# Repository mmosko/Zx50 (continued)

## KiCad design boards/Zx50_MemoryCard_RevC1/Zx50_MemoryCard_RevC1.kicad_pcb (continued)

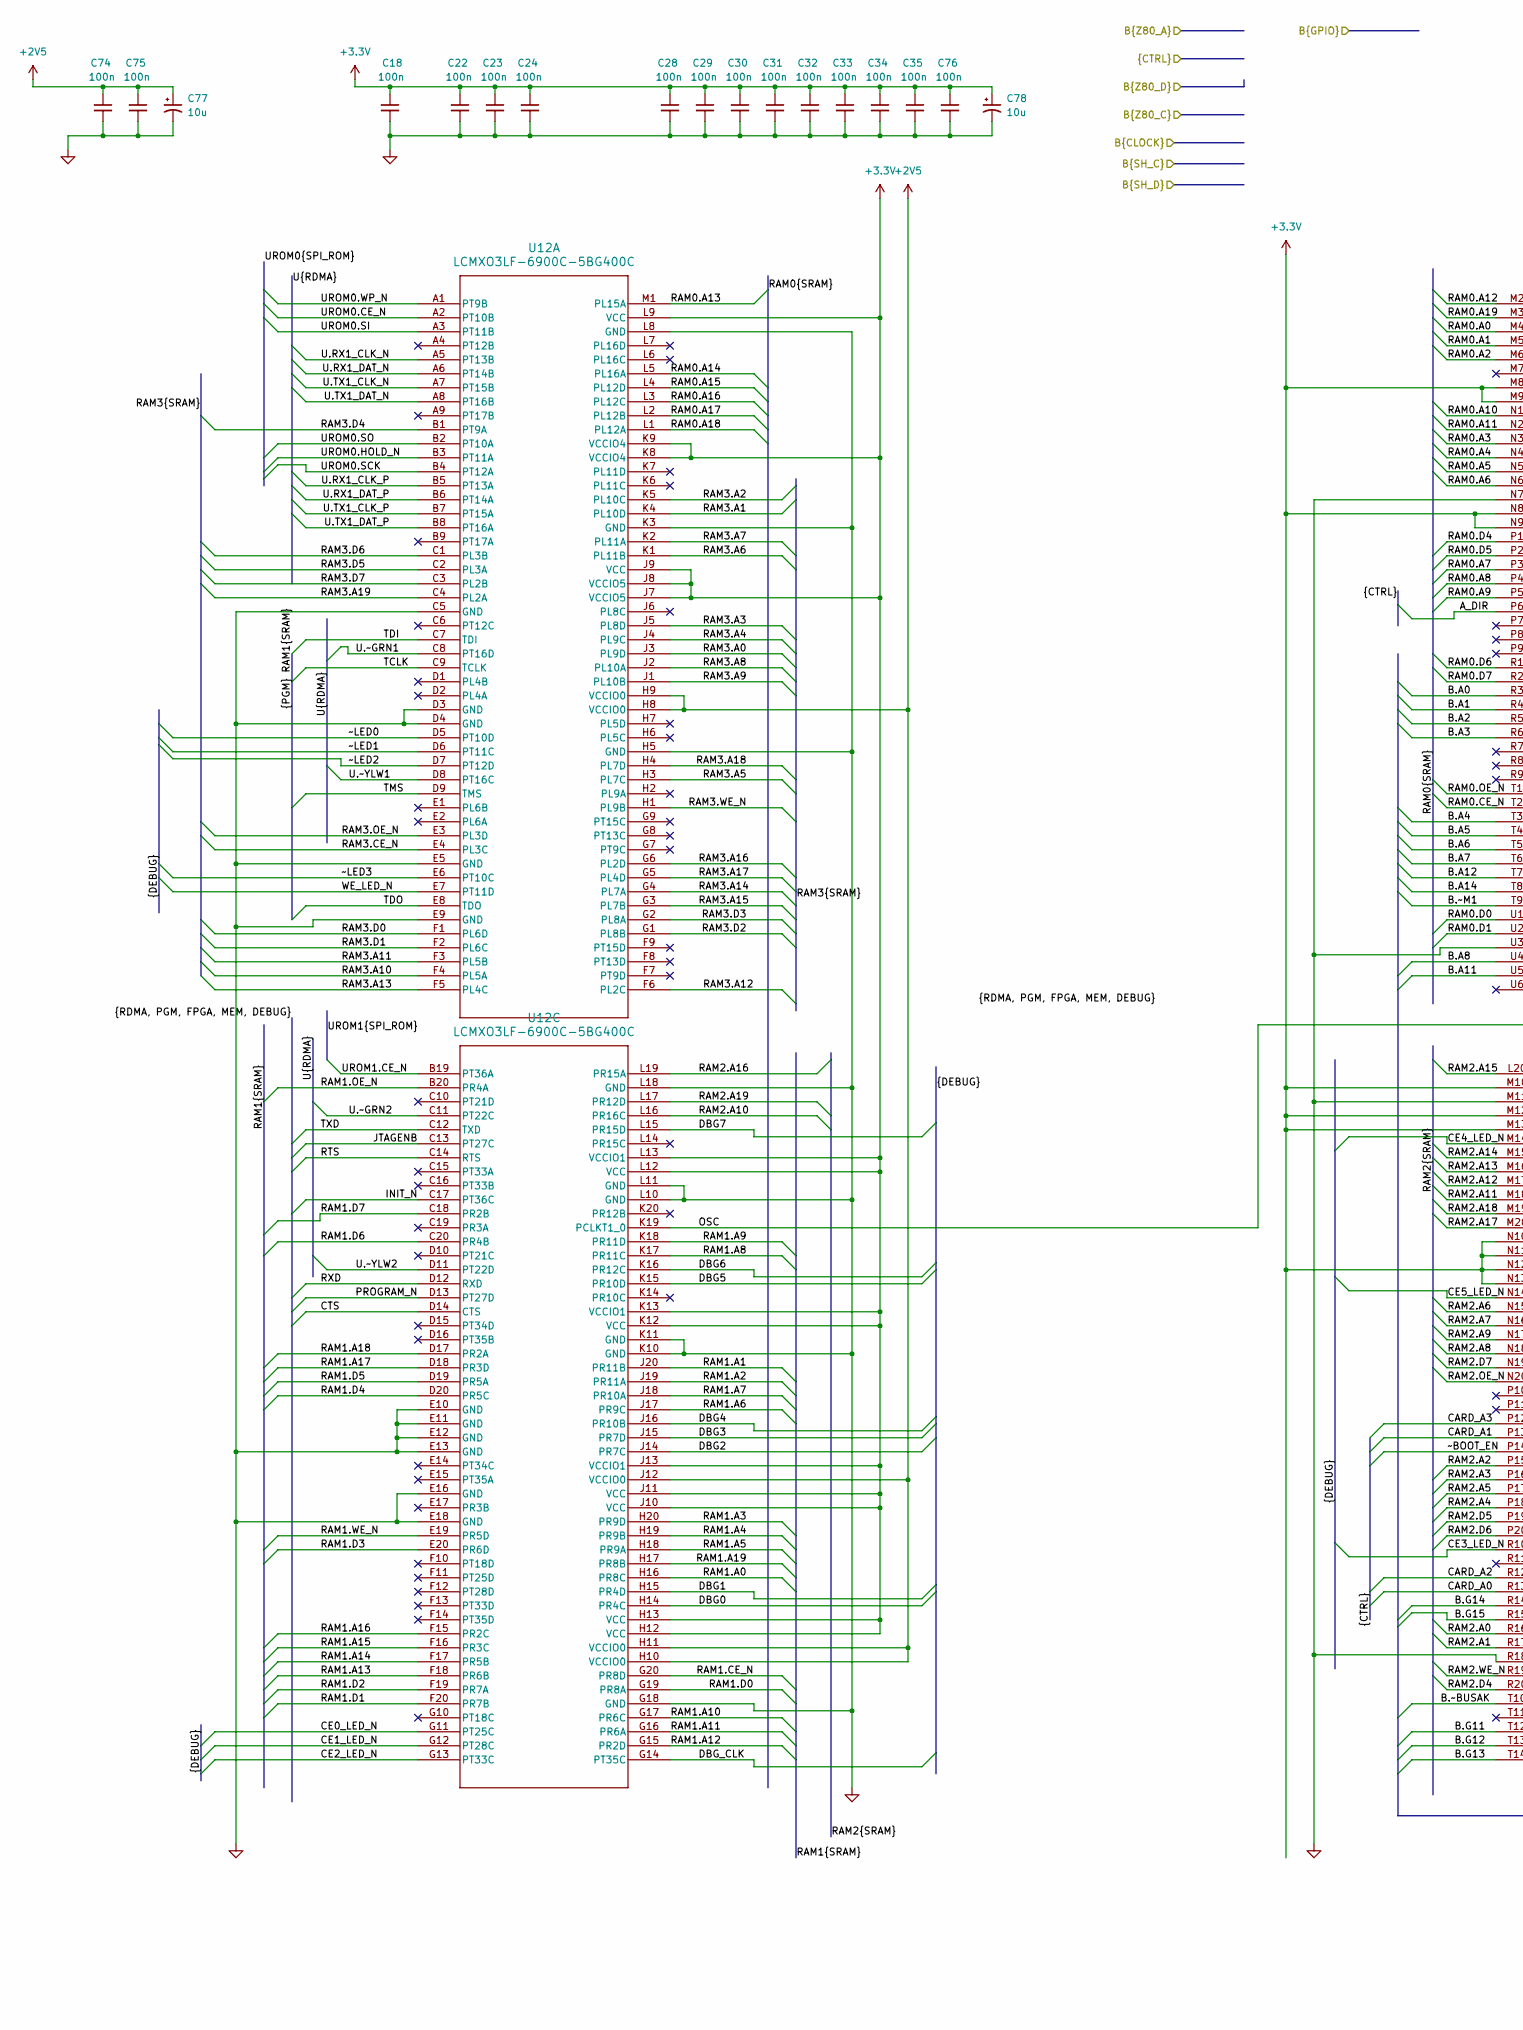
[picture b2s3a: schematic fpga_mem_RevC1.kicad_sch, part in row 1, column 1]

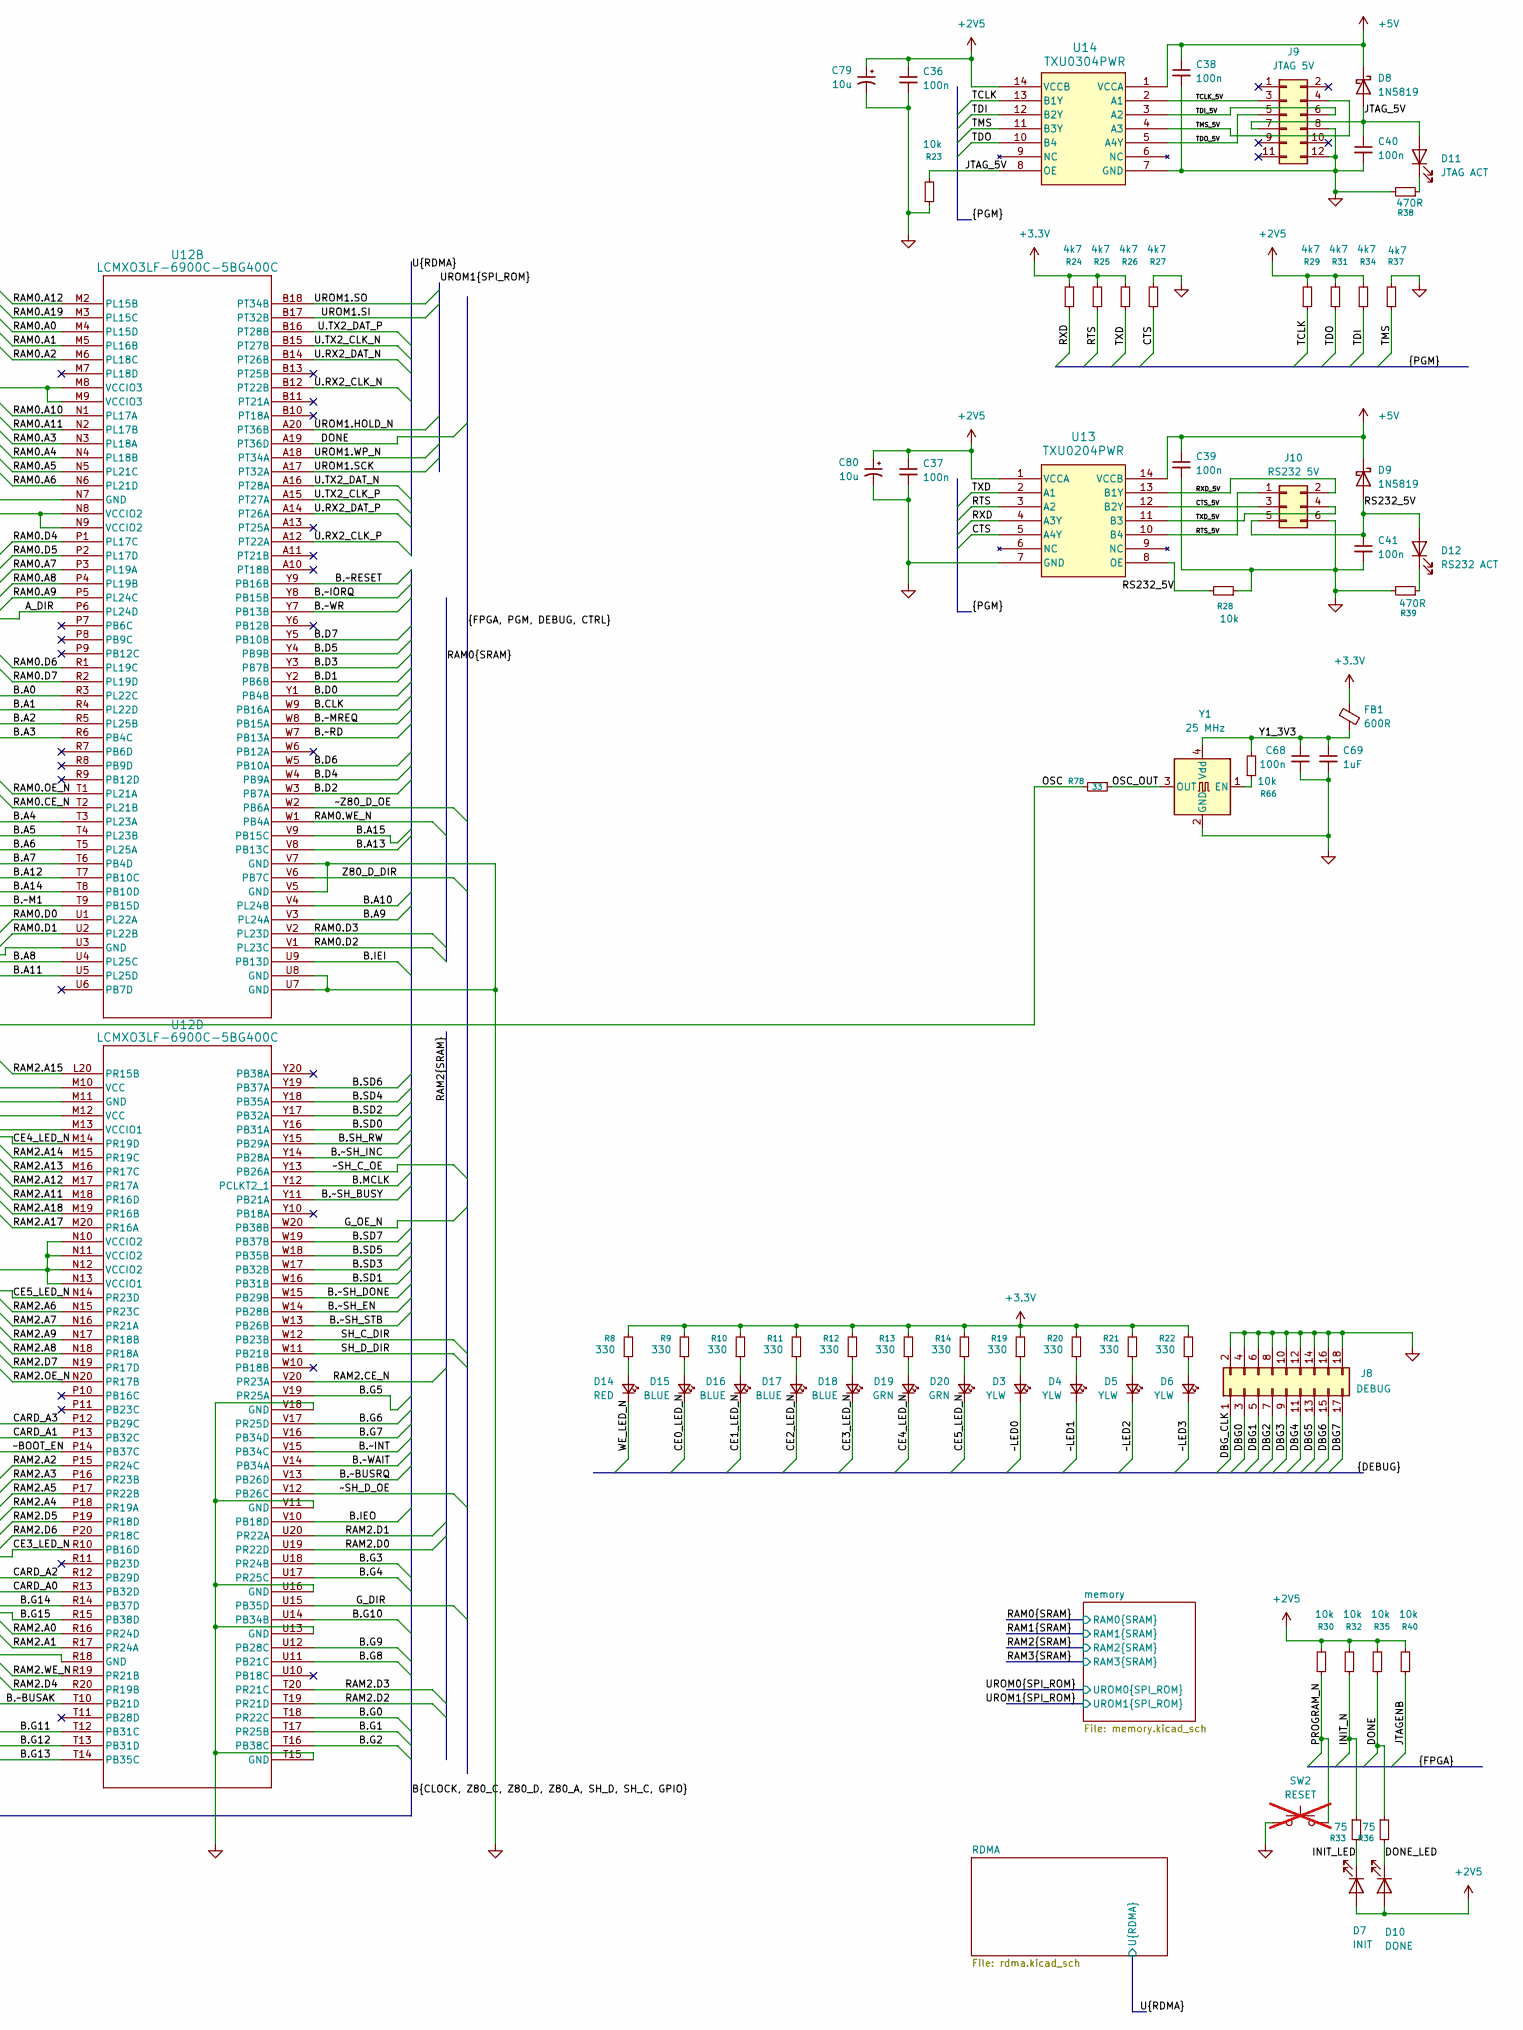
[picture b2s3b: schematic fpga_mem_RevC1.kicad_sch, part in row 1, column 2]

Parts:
C18, C22, C23, C24, C28, C29, C30, C31, C32, C33, C34, C35, C36, C37, C38, C39, C40, C41, C68, C74, C75, C76: 100n; C_0402_1005Metric; LCSC C1525
C69: 1uF; C_0402_1005Metric; LCSC C52923
C77, C78, C79, C80: 10u; C_1206_3216Metric; MFG PN AVX TAJA106K016RNJ Tantalinium; LCSC C7171
D3, D4, D5, D6: YLW; LED_0805_2012Metric; MFG_PN KT-0805Y; LCSC C2296
D7: INIT; LED_D3.0mm
D8, D9: 1N5819; D_SOD-323; LCSC C191023
D10: DONE; LED_D3.0mm
D11: JTAG ACT; LED_D3.0mm
D12: RS232 ACT; LED_D3.0mm
D14: RED; LED_0805_2012Metric; MFG_PN NCD0805R1; LCSC C84256
D15, D16, D17, D18: BLUE; LED_0805_2012Metric; MFG_PN KT-0805B; LCSC C2293
D19, D20: GRN; LED_0805_2012Metric; MFG_PN KT-0805G; LCSC C2297
FB1: 600R; 0805; LCSC C1017
J8: DEBUG; IDC-Header_2x09_P2.54mm_Vertical
J9: JTAG 5V; IDC-Header_2x06_P2.54mm_Horizontal
J10: RS232 5V; IDC-Header_2x03_P2.54mm_Horizontal
R8, R9, R10, R11, R12, R13, R14, R19, R20, R21, R22: 330; R_0805_2012Metric; MFG_PN 0805W8F3300T5E; LCSC C17630
R23, R28, R30, R32, R35, R40, R66: 10k; R_0402_1005Metric; MFG_PN 0402WGF1002TCE; LCSC C25744
R24, R25, R26, R27, R29, R31, R34, R37: 4k7; R_0402_1005Metric; MFG_PN 0402WGF4701TCE; LCSC C25900
R33, R36: 75; R_0603_1608Metric; MFG_PN 0603WAF750JT5E; LCSC C4275
R38, R39: 470R; R_0805_2012Metric; MFG_PN 0805W8F4700T5E; LCSC C17710
R78: 33; R_0402_1005Metric; MFG_PN 0402WGF1000TCE; LCSC C25076
SW2: RESET; SW_PUSH_6mm_H7.3mm; DigiKey_PN SW402-ND; not fitted
U12: LCMXO3LF-6900C-5BG400C; CABGA400_LAT
U13: TXU0204PWR; TSSOP14_PW_TEX; LCSC C4363888
U14: TXU0304PWR; TSSOP14_PW_TEX; LCSC C4364118
Y1: 25 MHz; Crystal_SMD_3225-4Pin_3.2x2.5mm; LCSC C669088

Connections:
+2V5: C36.1, C37.1, C74.1, C75.1, C77.1, C79.1, C80.1, D7.2 (A), D10.2 (A), R29.2, R30.2, R31.2, R32.2, R34.2, R35.2, R40.2, U12.H8 (VCCIO0), U12.H9 (VCCIO0), U12.H10 (VCCIO0), U12.H11 (VCCIO0), U12.J12 (VCCIO0), U13.1 (VCCA), U14.14 (VCCB); also elsewhere on the board
+3.3V: C18.1, C22.1, C23.1, C24.1, C28.1, C29.1, C30.1, C31.1, C32.1, C33.1, C34.1, C35.1, C76.1, C78.1, FB1.1, R8.2, R9.2, R10.2, R11.2, R12.2, R13.2, R14.2, R19.2, R20.2, R21.2, R22.2, R24.2, R25.2, R26.2, U12.H12 (VCC), U12.H13 (VCC), U12.J7 (VCCIO5), U12.J8 (VCCIO5), U12.J9 (VCC), U12.J10 (VCC), U12.J11 (VCC), U12.J13 (VCCIO1), U12.K8 (VCCIO4), U12.K9 (VCCIO4), U12.K12 (VCC), U12.K13 (VCCIO1), U12.L9 (VCC), U12.L12 (VCC), U12.L13 (VCCIO1), U12.M8 (VCCIO3), U12.M9 (VCCIO3), U12.M10 (VCC), U12.M12 (VCC), U12.M13 (VCCIO1), U12.N8 (VCCIO2), U12.N9 (VCCIO2), U12.N10 (VCCIO2), U12.N11 (VCCIO2), U12.N12 (VCCIO2), U12.N13 (VCCIO1); also elsewhere on the board
+5V: C38.1, C39.1, D8.1 (K), D9.1 (K), U13.14 (VCCB), U14.1 (VCCA); also elsewhere on the board
/A_DIR: U12.P6 (PL24D); also elsewhere on the board
/B.A0: U12.R3 (PL22C); also elsewhere on the board
/B.A1: U12.R4 (PL22D); also elsewhere on the board
/B.A2: U12.R5 (PL25B); also elsewhere on the board
/B.A3: U12.R6 (PB4C); also elsewhere on the board
/B.A4: U12.T3 (PL23A); also elsewhere on the board
/B.A5: U12.T4 (PL23B); also elsewhere on the board
/B.A6: U12.T5 (PL25A); also elsewhere on the board
/B.A7: U12.T6 (PB4D); also elsewhere on the board
/B.A8: U12.U4 (PL25C); also elsewhere on the board
/B.A9: U12.V3 (PL24A); also elsewhere on the board
/B.A10: U12.V4 (PL24B); also elsewhere on the board
/B.A11: U12.U5 (PL25D); also elsewhere on the board
/B.A12: U12.T7 (PB10C); also elsewhere on the board
/B.A13: U12.V8 (PB13C); also elsewhere on the board
/B.A14: U12.T8 (PB10D); also elsewhere on the board
/B.A15: U12.V9 (PB15C); also elsewhere on the board
/B.CLK: U12.W9 (PB16A); also elsewhere on the board
/B.D0: U12.Y1 (PB4B); also elsewhere on the board
/B.D1: U12.Y2 (PB6B); also elsewhere on the board
/B.D2: U12.W3 (PB7A); also elsewhere on the board
/B.D3: U12.Y3 (PB7B); also elsewhere on the board
/B.D4: U12.W4 (PB9A); also elsewhere on the board
/B.D5: U12.Y4 (PB9B); also elsewhere on the board
/B.D6: U12.W5 (PB10A); also elsewhere on the board
/B.D7: U12.Y5 (PB10B); also elsewhere on the board
/B.G0: U12.T18 (PR22C); also elsewhere on the board
/B.G1: U12.T17 (PR25B); also elsewhere on the board
/B.G2: U12.T16 (PB38C); also elsewhere on the board
/B.G3: U12.U18 (PR24B); also elsewhere on the board
/B.G4: U12.U17 (PR25C); also elsewhere on the board
/B.G5: U12.V19 (PR25A); also elsewhere on the board
/B.G6: U12.V17 (PR25D); also elsewhere on the board
/B.G7: U12.V16 (PB34D); also elsewhere on the board
/B.G8: U12.U11 (PB21C); also elsewhere on the board
/B.G9: U12.U12 (PB28C); also elsewhere on the board
/B.G10: U12.U14 (PB34B); also elsewhere on the board
/B.G11: U12.T12 (PB31C); also elsewhere on the board
/B.G12: U12.T13 (PB31D); also elsewhere on the board
/B.G13: U12.T14 (PB35C); also elsewhere on the board
/B.G14: U12.R14 (PB37D); also elsewhere on the board
/B.G15: U12.R15 (PB38D); also elsewhere on the board
/B.IEI: U12.U9 (PB13D); also elsewhere on the board
/B.IEO: U12.V10 (PB18D); also elsewhere on the board
/B.MCLK: U12.Y12 (PCLKT2_1); also elsewhere on the board
/B.SD0: U12.Y16 (PB31A); also elsewhere on the board
/B.SD1: U12.W16 (PB31B); also elsewhere on the board
/B.SD2: U12.Y17 (PB32A); also elsewhere on the board
/B.SD3: U12.W17 (PB32B); also elsewhere on the board
/B.SD4: U12.Y18 (PB35A); also elsewhere on the board
/B.SD5: U12.W18 (PB35B); also elsewhere on the board
/B.SD6: U12.Y19 (PB37A); also elsewhere on the board
/B.SD7: U12.W19 (PB37B); also elsewhere on the board
/B.SH_RW: U12.Y15 (PB29A); also elsewhere on the board
/B.~BUSAK: U12.T10 (PB21D); also elsewhere on the board
/B.~BUSRQ: U12.V13 (PB26D); also elsewhere on the board
/B.~INT: U12.V15 (PB34C); also elsewhere on the board
/B.~IORQ: U12.Y8 (PB15B); also elsewhere on the board
/B.~M1: U12.T9 (PB15D); also elsewhere on the board
/B.~MREQ: U12.W8 (PB15A); also elsewhere on the board
/B.~RD: U12.W7 (PB13A); also elsewhere on the board
/B.~RESET: U12.Y9 (PB16B); also elsewhere on the board
/B.~SH_BUSY: U12.Y11 (PB21A); also elsewhere on the board
/B.~SH_DONE: U12.W15 (PB29B); also elsewhere on the board
/B.~SH_EN: U12.W14 (PB28B); also elsewhere on the board
/B.~SH_INC: U12.Y14 (PB28A); also elsewhere on the board
/B.~SH_STB: U12.W13 (PB26B); also elsewhere on the board
/B.~WAIT: U12.V14 (PB34A); also elsewhere on the board
/B.~WR: U12.Y7 (PB13B); also elsewhere on the board
/CARD_A0: U12.R13 (PB32D); also elsewhere on the board
/CARD_A1: U12.P13 (PB32C); also elsewhere on the board
/CARD_A2: U12.R12 (PB29D); also elsewhere on the board
/CARD_A3: U12.P12 (PB29C); also elsewhere on the board
/FPGA/CE0_LED_N: D15.1 (K), U12.G11 (PT25C)
/FPGA/CE1_LED_N: D16.1 (K), U12.G12 (PT28C)
/FPGA/CE2_LED_N: D17.1 (K), U12.G13 (PT33C)
/FPGA/CE3_LED_N: D18.1 (K), U12.R10 (PB16D)
/FPGA/CE4_LED_N: D19.1 (K), U12.M14 (PR19D)
/FPGA/CE5_LED_N: D20.1 (K), U12.N14 (PR23D)
/FPGA/CTS: R27.1, U12.D14 (CTS), U13.5 (A4Y)
/FPGA/CTS_5V: J10.3, U13.12 (B2Y)
/FPGA/DBG0: J8.3, U12.H14 (PR4C)
/FPGA/DBG1: J8.5, U12.H15 (PR4D)
/FPGA/DBG2: J8.7, U12.J14 (PR7C)
/FPGA/DBG3: J8.9, U12.J15 (PR7D)
/FPGA/DBG4: J8.11, U12.J16 (PR10B)
/FPGA/DBG5: J8.13, U12.K15 (PR10D)
/FPGA/DBG6: J8.15, U12.K16 (PR12C)
/FPGA/DBG7: J8.17, U12.L15 (PR15D)
/FPGA/DBG_CLK: J8.1, U12.G14 (PT35C)
/FPGA/DONE: R35.1, R36.1, U12.A19 (PT36D)
/FPGA/DONE_LED: D10.1 (K), R36.2
/FPGA/INIT_LED: D7.1 (K), R33.2
/FPGA/INIT_N: R32.1, R33.1, U12.C17 (PT36C)
/FPGA/JTAGENB: R40.1, U12.C13 (PT27C)
/FPGA/JTAG_5V: C40.1, D8.2 (A), D11.2 (A), J9.7, R23.2, U14.8 (OE)
/FPGA/OSC: R78.2, U12.K19 (PCLKT1_0)
/FPGA/OSC_OUT: R78.1, Y1.3 (OUT)
/FPGA/PROGRAM_N: R30.1, SW2.2, U12.D13 (PT27D)
/FPGA/RAM0.A0: U12.M4 (PL15D); also elsewhere on the board
/FPGA/RAM0.A1: U12.M5 (PL16B); also elsewhere on the board
/FPGA/RAM0.A2: U12.M6 (PL18C); also elsewhere on the board
/FPGA/RAM0.A3: U12.N3 (PL18A); also elsewhere on the board
/FPGA/RAM0.A4: U12.N4 (PL18B); also elsewhere on the board
/FPGA/RAM0.A5: U12.N5 (PL21C); also elsewhere on the board
/FPGA/RAM0.A6: U12.N6 (PL21D); also elsewhere on the board
/FPGA/RAM0.A7: U12.P3 (PL19A); also elsewhere on the board
/FPGA/RAM0.A8: U12.P4 (PL19B); also elsewhere on the board
/FPGA/RAM0.A9: U12.P5 (PL24C); also elsewhere on the board
/FPGA/RAM0.A10: U12.N1 (PL17A); also elsewhere on the board
/FPGA/RAM0.A11: U12.N2 (PL17B); also elsewhere on the board
/FPGA/RAM0.A12: U12.M2 (PL15B); also elsewhere on the board
/FPGA/RAM0.A13: U12.M1 (PL15A); also elsewhere on the board
/FPGA/RAM0.A14: U12.L5 (PL16A); also elsewhere on the board
/FPGA/RAM0.A15: U12.L4 (PL12D); also elsewhere on the board
/FPGA/RAM0.A16: U12.L3 (PL12C); also elsewhere on the board
/FPGA/RAM0.A17: U12.L2 (PL12B); also elsewhere on the board
/FPGA/RAM0.A18: U12.L1 (PL12A); also elsewhere on the board
/FPGA/RAM0.A19: U12.M3 (PL15C); also elsewhere on the board
/FPGA/RAM0.CE_N: U12.T2 (PL21B); also elsewhere on the board
/FPGA/RAM0.D0: U12.U1 (PL22A); also elsewhere on the board
/FPGA/RAM0.D1: U12.U2 (PL22B); also elsewhere on the board
/FPGA/RAM0.D2: U12.V1 (PL23C); also elsewhere on the board
/FPGA/RAM0.D3: U12.V2 (PL23D); also elsewhere on the board
/FPGA/RAM0.D4: U12.P1 (PL17C); also elsewhere on the board
/FPGA/RAM0.D5: U12.P2 (PL17D); also elsewhere on the board
/FPGA/RAM0.D6: U12.R1 (PL19C); also elsewhere on the board
/FPGA/RAM0.D7: U12.R2 (PL19D); also elsewhere on the board
/FPGA/RAM0.OE_N: U12.T1 (PL21A); also elsewhere on the board
/FPGA/RAM0.WE_N: U12.W1 (PB4A); also elsewhere on the board
/FPGA/RAM1.A0: U12.H16 (PR8C); also elsewhere on the board
/FPGA/RAM1.A1: U12.J20 (PR11B); also elsewhere on the board
/FPGA/RAM1.A2: U12.J19 (PR11A); also elsewhere on the board
/FPGA/RAM1.A3: U12.H20 (PR9D); also elsewhere on the board
/FPGA/RAM1.A4: U12.H19 (PR9B); also elsewhere on the board
/FPGA/RAM1.A5: U12.H18 (PR9A); also elsewhere on the board
/FPGA/RAM1.A6: U12.J17 (PR9C); also elsewhere on the board
/FPGA/RAM1.A7: U12.J18 (PR10A); also elsewhere on the board
/FPGA/RAM1.A8: U12.K17 (PR11C); also elsewhere on the board
/FPGA/RAM1.A9: U12.K18 (PR11D); also elsewhere on the board
/FPGA/RAM1.A10: U12.G17 (PR6C); also elsewhere on the board
/FPGA/RAM1.A11: U12.G16 (PR6A); also elsewhere on the board
/FPGA/RAM1.A12: U12.G15 (PR2D); also elsewhere on the board
/FPGA/RAM1.A13: U12.F18 (PR6B); also elsewhere on the board
/FPGA/RAM1.A14: U12.F17 (PR5B); also elsewhere on the board
/FPGA/RAM1.A15: U12.F16 (PR3C); also elsewhere on the board
/FPGA/RAM1.A16: U12.F15 (PR2C); also elsewhere on the board
/FPGA/RAM1.A17: U12.D18 (PR3D); also elsewhere on the board
/FPGA/RAM1.A18: U12.D17 (PR2A); also elsewhere on the board
/FPGA/RAM1.A19: U12.H17 (PR8B); also elsewhere on the board
/FPGA/RAM1.CE_N: U12.G20 (PR8D); also elsewhere on the board
/FPGA/RAM1.D0: U12.G19 (PR8A); also elsewhere on the board
/FPGA/RAM1.D1: U12.F20 (PR7B); also elsewhere on the board
/FPGA/RAM1.D2: U12.F19 (PR7A); also elsewhere on the board
/FPGA/RAM1.D3: U12.E20 (PR6D); also elsewhere on the board
/FPGA/RAM1.D4: U12.D20 (PR5C); also elsewhere on the board
/FPGA/RAM1.D5: U12.D19 (PR5A); also elsewhere on the board
/FPGA/RAM1.D6: U12.C20 (PR4B); also elsewhere on the board
/FPGA/RAM1.D7: U12.C18 (PR2B); also elsewhere on the board
/FPGA/RAM1.OE_N: U12.B20 (PR4A); also elsewhere on the board
/FPGA/RAM1.WE_N: U12.E19 (PR5D); also elsewhere on the board
/FPGA/RAM2.A0: U12.R16 (PR24D); also elsewhere on the board
/FPGA/RAM2.A1: U12.R17 (PR24A); also elsewhere on the board
/FPGA/RAM2.A2: U12.P15 (PR24C); also elsewhere on the board
/FPGA/RAM2.A3: U12.P16 (PR23B); also elsewhere on the board
/FPGA/RAM2.A4: U12.P18 (PR19A); also elsewhere on the board
/FPGA/RAM2.A5: U12.P17 (PR22B); also elsewhere on the board
/FPGA/RAM2.A6: U12.N15 (PR23C); also elsewhere on the board
/FPGA/RAM2.A7: U12.N16 (PR21A); also elsewhere on the board
/FPGA/RAM2.A8: U12.N18 (PR18A); also elsewhere on the board
/FPGA/RAM2.A9: U12.N17 (PR18B); also elsewhere on the board
/FPGA/RAM2.A10: U12.L16 (PR16C); also elsewhere on the board
/FPGA/RAM2.A11: U12.M18 (PR16D); also elsewhere on the board
/FPGA/RAM2.A12: U12.M17 (PR17A); also elsewhere on the board
/FPGA/RAM2.A13: U12.M16 (PR17C); also elsewhere on the board
/FPGA/RAM2.A14: U12.M15 (PR19C); also elsewhere on the board
/FPGA/RAM2.A15: U12.L20 (PR15B); also elsewhere on the board
/FPGA/RAM2.A16: U12.L19 (PR15A); also elsewhere on the board
/FPGA/RAM2.A17: U12.M20 (PR16A); also elsewhere on the board
/FPGA/RAM2.A18: U12.M19 (PR16B); also elsewhere on the board
/FPGA/RAM2.A19: U12.L17 (PR12D); also elsewhere on the board
/FPGA/RAM2.CE_N: U12.V20 (PR23A); also elsewhere on the board
/FPGA/RAM2.D0: U12.U19 (PR22D); also elsewhere on the board
/FPGA/RAM2.D1: U12.U20 (PR22A); also elsewhere on the board
/FPGA/RAM2.D2: U12.T19 (PR21D); also elsewhere on the board
/FPGA/RAM2.D3: U12.T20 (PR21C); also elsewhere on the board
/FPGA/RAM2.D4: U12.R20 (PR19B); also elsewhere on the board
/FPGA/RAM2.D5: U12.P19 (PR18D); also elsewhere on the board
/FPGA/RAM2.D6: U12.P20 (PR18C); also elsewhere on the board
/FPGA/RAM2.D7: U12.N19 (PR17D); also elsewhere on the board
/FPGA/RAM2.OE_N: U12.N20 (PR17B); also elsewhere on the board
/FPGA/RAM2.WE_N: U12.R19 (PR21B); also elsewhere on the board
/FPGA/RAM3.A0: U12.J3 (PL9D); also elsewhere on the board
/FPGA/RAM3.A1: U12.K4 (PL10D); also elsewhere on the board
/FPGA/RAM3.A2: U12.K5 (PL10C); also elsewhere on the board
/FPGA/RAM3.A3: U12.J5 (PL8D); also elsewhere on the board
/FPGA/RAM3.A4: U12.J4 (PL9C); also elsewhere on the board
/FPGA/RAM3.A5: U12.H3 (PL7C); also elsewhere on the board
/FPGA/RAM3.A6: U12.K1 (PL11B); also elsewhere on the board
/FPGA/RAM3.A7: U12.K2 (PL11A); also elsewhere on the board
/FPGA/RAM3.A8: U12.J2 (PL10A); also elsewhere on the board
/FPGA/RAM3.A9: U12.J1 (PL10B); also elsewhere on the board
/FPGA/RAM3.A10: U12.F4 (PL5A); also elsewhere on the board
/FPGA/RAM3.A11: U12.F3 (PL5B); also elsewhere on the board
/FPGA/RAM3.A12: U12.F6 (PL2C); also elsewhere on the board
/FPGA/RAM3.A13: U12.F5 (PL4C); also elsewhere on the board
/FPGA/RAM3.A14: U12.G4 (PL7A); also elsewhere on the board
/FPGA/RAM3.A15: U12.G3 (PL7B); also elsewhere on the board
/FPGA/RAM3.A16: U12.G6 (PL2D); also elsewhere on the board
/FPGA/RAM3.A17: U12.G5 (PL4D); also elsewhere on the board
/FPGA/RAM3.A18: U12.H4 (PL7D); also elsewhere on the board
/FPGA/RAM3.A19: U12.C4 (PL2A); also elsewhere on the board
/FPGA/RAM3.CE_N: U12.E4 (PL3C); also elsewhere on the board
/FPGA/RAM3.D0: U12.F1 (PL6D); also elsewhere on the board
/FPGA/RAM3.D1: U12.F2 (PL6C); also elsewhere on the board
/FPGA/RAM3.D2: U12.G1 (PL8B); also elsewhere on the board
/FPGA/RAM3.D3: U12.G2 (PL8A); also elsewhere on the board
/FPGA/RAM3.D4: U12.B1 (PT9A); also elsewhere on the board
/FPGA/RAM3.D5: U12.C2 (PL3A); also elsewhere on the board
/FPGA/RAM3.D6: U12.C1 (PL3B); also elsewhere on the board
/FPGA/RAM3.D7: U12.C3 (PL2B); also elsewhere on the board
/FPGA/RAM3.OE_N: U12.E3 (PL3D); also elsewhere on the board
/FPGA/RAM3.WE_N: U12.H1 (PL9B); also elsewhere on the board
/FPGA/RS232_5V: C41.1, D9.2 (A), D12.2 (A), J10.5, R28.2, U13.8 (OE)
/FPGA/RTS: R25.1, U12.C14 (RTS), U13.3 (A2)
/FPGA/RTS_5V: J10.1, U13.10 (B4)
/FPGA/RXD: R24.1, U12.D12 (RXD), U13.4 (A3Y)
/FPGA/RXD_5V: J10.2, U13.13 (B1Y)
/FPGA/TCLK: R29.1, U12.C9 (TCLK), U14.13 (B1Y)
/FPGA/TCLK_5V: J9.3, U14.2 (A1)
/FPGA/TDI: R34.1, U12.C7 (TDI), U14.12 (B2Y)
/FPGA/TDI_5V: J9.6, U14.3 (A2)
/FPGA/TDO: R31.1, U12.E8 (TDO), U14.10 (B4)
/FPGA/TDO_5V: J9.5, U14.5 (A4Y)
/FPGA/TMS: R37.1, U12.D9 (TMS), U14.11 (B3Y)
/FPGA/TMS_5V: J9.4, U14.4 (A3)
/FPGA/TXD: R26.1, U12.C12 (TXD), U13.2 (A1)
/FPGA/TXD_5V: J10.4, U13.11 (B3)
/FPGA/U.RX1_CLK_N: U12.A5 (PT13B); also elsewhere on the board
/FPGA/U.RX1_CLK_P: U12.B5 (PT13A); also elsewhere on the board
/FPGA/U.RX1_DAT_N: U12.A6 (PT14B); also elsewhere on the board
/FPGA/U.RX1_DAT_P: U12.B6 (PT14A); also elsewhere on the board
/FPGA/U.RX2_CLK_N: U12.B12 (PT22B); also elsewhere on the board
/FPGA/U.RX2_CLK_P: U12.A12 (PT22A); also elsewhere on the board
/FPGA/U.RX2_DAT_N: U12.B14 (PT26B); also elsewhere on the board
/FPGA/U.RX2_DAT_P: U12.A14 (PT26A); also elsewhere on the board
/FPGA/U.TX1_CLK_N: U12.A7 (PT15B); also elsewhere on the board
/FPGA/U.TX1_CLK_P: U12.B7 (PT15A); also elsewhere on the board
/FPGA/U.TX1_DAT_N: U12.A8 (PT16B); also elsewhere on the board
/FPGA/U.TX1_DAT_P: U12.B8 (PT16A); also elsewhere on the board
/FPGA/U.TX2_CLK_N: U12.B15 (PT27B); also elsewhere on the board
/FPGA/U.TX2_CLK_P: U12.A15 (PT27A); also elsewhere on the board
/FPGA/U.TX2_DAT_N: U12.A16 (PT28A); also elsewhere on the board
/FPGA/U.TX2_DAT_P: U12.B16 (PT28B); also elsewhere on the board
/FPGA/U.~GRN1: U12.C8 (PT16D); also elsewhere on the board
/FPGA/U.~GRN2: U12.C11 (PT22C); also elsewhere on the board
/FPGA/U.~YLW1: U12.D8 (PT16C); also elsewhere on the board
/FPGA/U.~YLW2: U12.D11 (PT22D); also elsewhere on the board
/FPGA/UROM0.CE_N: U12.A2 (PT10B); also elsewhere on the board
/FPGA/UROM0.HOLD_N: U12.B3 (PT11A); also elsewhere on the board
/FPGA/UROM0.SCK: U12.B4 (PT12A); also elsewhere on the board
/FPGA/UROM0.SI: U12.A3 (PT11B); also elsewhere on the board
/FPGA/UROM0.SO: U12.B2 (PT10A); also elsewhere on the board
/FPGA/UROM0.WP_N: U12.A1 (PT9B); also elsewhere on the board
/FPGA/UROM1.CE_N: U12.B19 (PT36A); also elsewhere on the board
/FPGA/UROM1.HOLD_N: U12.A20 (PT36B); also elsewhere on the board
/FPGA/UROM1.SCK: U12.A17 (PT32A); also elsewhere on the board
/FPGA/UROM1.SI: U12.B17 (PT32B); also elsewhere on the board
/FPGA/UROM1.SO: U12.B18 (PT34B); also elsewhere on the board
/FPGA/UROM1.WP_N: U12.A18 (PT34A); also elsewhere on the board
/FPGA/WE_LED_N: D14.1 (K), U12.E7 (PT11D)
/FPGA/Y1_3V3: C68.1, C69.1, FB1.2, R66.2, Y1.4 (Vdd)
/FPGA/~LED0: D3.1 (K), U12.D5 (PT10D)
/FPGA/~LED1: D4.1 (K), U12.D6 (PT11C)
/FPGA/~LED2: D5.1 (K), U12.D7 (PT12D)
/FPGA/~LED3: D6.1 (K), U12.E6 (PT10C)
/G_DIR: U12.U15 (PB35D); also elsewhere on the board
/G_OE_N: U12.W20 (PB38B); also elsewhere on the board
/SH_C_DIR: U12.W12 (PB23B); also elsewhere on the board
/SH_D_DIR: U12.W11 (PB21B); also elsewhere on the board
/Z80_D_DIR: U12.V6 (PB7C); also elsewhere on the board
/~BOOT_EN: U12.P14 (PB37C); also elsewhere on the board
/~SH_C_OE: U12.Y13 (PB26A); also elsewhere on the board
/~SH_D_OE: U12.V12 (PB26C); also elsewhere on the board
/~Z80_D_OE: U12.W2 (PB6A); also elsewhere on the board
GND: C18.2, C22.2, C23.2, C24.2, C28.2, C29.2, C30.2, C31.2, C32.2, C33.2, C34.2, C35.2, C36.2, C37.2, C38.2, C39.2, C40.2, C41.2, C68.2, C69.2, C74.2, C75.2, C76.2, C77.2, C78.2, C79.2, C80.2, J8.2, J8.4, J8.6, J8.8, J8.10, J8.12, J8.14, J8.16, J8.18, J9.8, J9.12, J10.6, R23.1, R27.2, R28.1, R37.2, R38.2, R39.2, SW2.1, U12.C5 (GND), U12.D3 (GND), U12.D4 (GND), U12.E5 (GND), U12.E9 (GND), U12.E10 (GND), U12.E11 (GND), U12.E12 (GND), U12.E13 (GND), U12.E16 (GND), U12.E18 (GND), U12.G18 (GND), U12.H5 (GND), U12.K3 (GND), U12.K10 (GND), U12.K11 (GND), U12.L8 (GND), U12.L10 (GND), U12.L11 (GND), U12.L18 (GND), U12.M11 (GND), U12.N7 (GND), U12.R18 (GND), U12.T15 (GND), U12.U3 (GND), U12.U7 (GND), U12.U8 (GND), U12.U13 (GND), U12.U16 (GND), U12.V5 (GND), U12.V7 (GND), U12.V11 (GND), U12.V18 (GND), U13.7 (GND), U14.7 (GND), Y1.2 (GND); also elsewhere on the board
unnamed: D3.2 (A), R19.1
unnamed: D4.2 (A), R20.1
unnamed: D5.2 (A), R21.1
unnamed: D6.2 (A), R22.1
unnamed: D11.1 (K), R38.1
unnamed: D12.1 (K), R39.1
unnamed: D14.2 (A), R8.1
unnamed: D15.2 (A), R9.1
unnamed: D16.2 (A), R10.1
unnamed: D17.2 (A), R11.1
unnamed: D18.2 (A), R12.1
unnamed: D19.2 (A), R13.1
unnamed: D20.2 (A), R14.1
unnamed: R66.1, Y1.1 (EN)

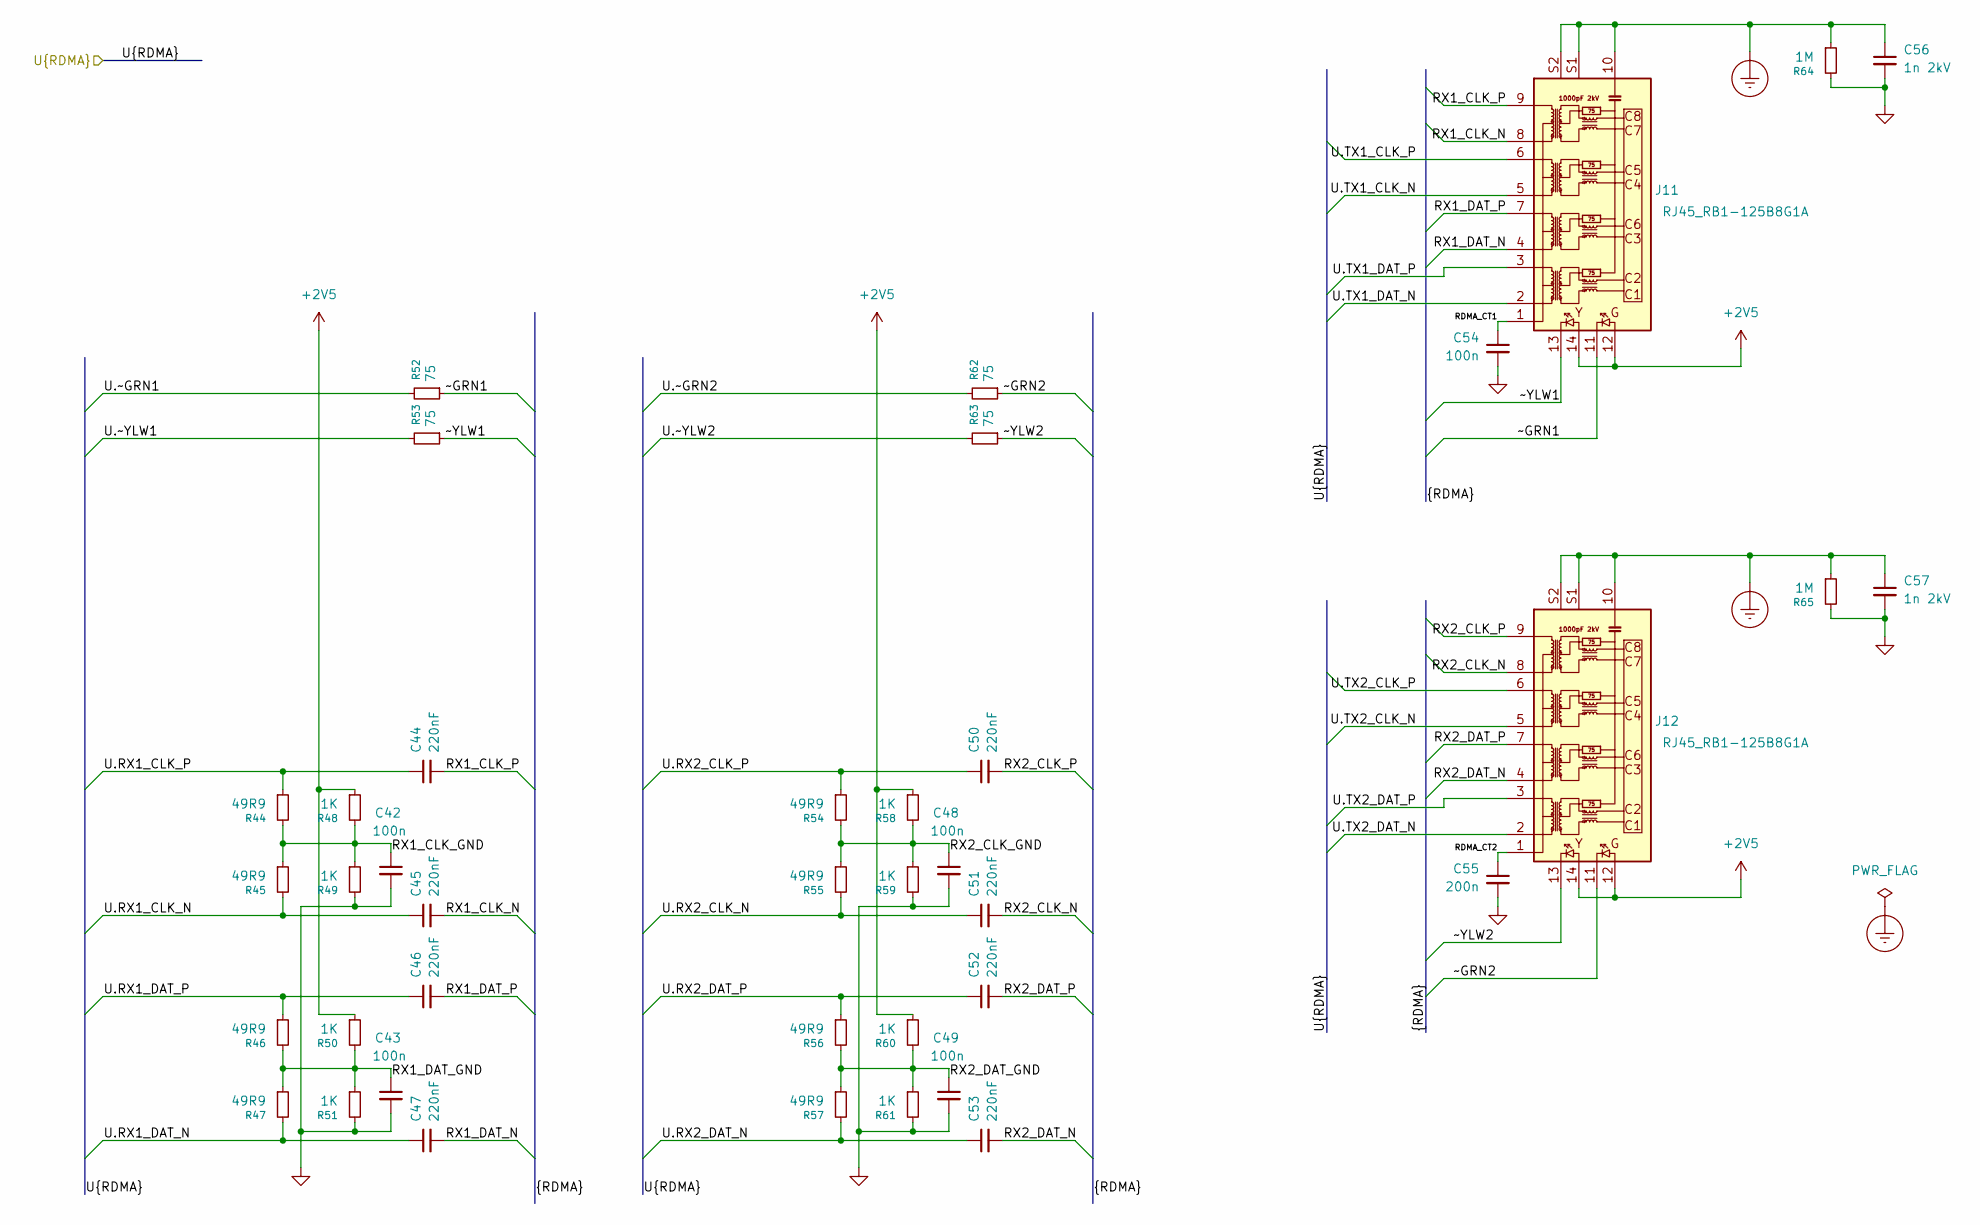
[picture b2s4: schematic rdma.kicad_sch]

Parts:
C42, C43, C48, C49, C54: 100n; C_0402_1005Metric; LCSC C1525
C44, C45, C46, C47, C50, C51, C52, C53: 220nF; C_0402_1005Metric; LCSC C16772
C55: 200n; C_0402_1005Metric; LCSC C1525
C56, C57: 1n 2kV; C_1206_3216Metric; LCSC C9196
J11, J12: RJ45_RB1-125B8G1A; HANRUN_HR911130A; MFG_PN HR911130C; LCSC C50933
R44, R45, R46, R47, R54, R55, R56, R57: 49R9; R_0402_1005Metric; MFG_PN 0402WGF499JTCE; LCSC C25120
R48, R49, R50, R51, R58, R59, R60, R61: 1K; R_0402_1005Metric; MFG_PN 0402WGF1001TCE; LCSC C11702
R52, R53, R62, R63: 75; R_0603_1608Metric; MFG_PN 0603WAF750JT5E; LCSC C4275
R64, R65: 1M; R_0805_2012Metric; MFG_PN 0805W8F1004T5E; LCSC C17514

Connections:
+2V5: J11.12, J11.14, J12.12, J12.14, R48.1, R50.1, R58.1, R60.1; also elsewhere on the board
/FPGA/RDMA/RDMA_CT1: C54.1, J11.1 (CT)
/FPGA/RDMA/RDMA_CT2: C55.1, J12.1 (CT)
/FPGA/RDMA/RX1_CLK_GND: C42.1, R44.2, R45.1, R48.2, R49.1
/FPGA/RDMA/RX1_CLK_N: C45.2, J11.8 (TD4+)
/FPGA/RDMA/RX1_CLK_P: C44.2, J11.9 (TD4-)
/FPGA/RDMA/RX1_DAT_GND: C43.1, R46.2, R47.1, R50.2, R51.1
/FPGA/RDMA/RX1_DAT_N: C47.2, J11.4 (TD2+)
/FPGA/RDMA/RX1_DAT_P: C46.2, J11.7 (TD2-)
/FPGA/RDMA/RX2_CLK_GND: C48.1, R54.2, R55.1, R58.2, R59.1
/FPGA/RDMA/RX2_CLK_N: C51.2, J12.8 (TD4+)
/FPGA/RDMA/RX2_CLK_P: C50.2, J12.9 (TD4-)
/FPGA/RDMA/RX2_DAT_GND: C49.1, R56.2, R57.1, R60.2, R61.1
/FPGA/RDMA/RX2_DAT_N: C53.2, J12.4 (TD2+)
/FPGA/RDMA/RX2_DAT_P: C52.2, J12.7 (TD2-)
/FPGA/RDMA/~GRN1: J11.11, R52.1
/FPGA/RDMA/~GRN2: J12.11, R62.1
/FPGA/RDMA/~YLW1: J11.13, R53.1
/FPGA/RDMA/~YLW2: J12.13, R63.1
/FPGA/U.RX1_CLK_N: C45.1, R45.2; also elsewhere on the board
/FPGA/U.RX1_CLK_P: C44.1, R44.1; also elsewhere on the board
/FPGA/U.RX1_DAT_N: C47.1, R47.2; also elsewhere on the board
/FPGA/U.RX1_DAT_P: C46.1, R46.1; also elsewhere on the board
/FPGA/U.RX2_CLK_N: C51.1, R55.2; also elsewhere on the board
/FPGA/U.RX2_CLK_P: C50.1, R54.1; also elsewhere on the board
/FPGA/U.RX2_DAT_N: C53.1, R57.2; also elsewhere on the board
/FPGA/U.RX2_DAT_P: C52.1, R56.1; also elsewhere on the board
/FPGA/U.TX1_CLK_N: J11.5 (TD3+); also elsewhere on the board
/FPGA/U.TX1_CLK_P: J11.6 (TD3-); also elsewhere on the board
/FPGA/U.TX1_DAT_N: J11.2 (TD1+); also elsewhere on the board
/FPGA/U.TX1_DAT_P: J11.3 (TD1-); also elsewhere on the board
/FPGA/U.TX2_CLK_N: J12.5 (TD3+); also elsewhere on the board
/FPGA/U.TX2_CLK_P: J12.6 (TD3-); also elsewhere on the board
/FPGA/U.TX2_DAT_N: J12.2 (TD1+); also elsewhere on the board
/FPGA/U.TX2_DAT_P: J12.3 (TD1-); also elsewhere on the board
/FPGA/U.~GRN1: R52.2; also elsewhere on the board
/FPGA/U.~GRN2: R62.2; also elsewhere on the board
/FPGA/U.~YLW1: R53.2; also elsewhere on the board
/FPGA/U.~YLW2: R63.2; also elsewhere on the board
Earth_Protective: C56.1, C57.1, J11.10 (GND), J11.S1, J11.S2, J12.10 (GND), J12.S1, J12.S2, R64.1, R65.1
GND: C42.2, C43.2, C48.2, C49.2, C54.2, C55.2, C56.2, C57.2, R49.2, R51.2, R59.2, R61.2, R64.2, R65.2; also elsewhere on the board
